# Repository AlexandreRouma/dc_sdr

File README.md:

# DEFCON SDR Badge

The firmware included here is not finished and the hardware isn't fully tested. Use at your own risk.

Make sure to read the license (the file is `/license`). The entire content of this repository is **NOT for commercial purposes**.

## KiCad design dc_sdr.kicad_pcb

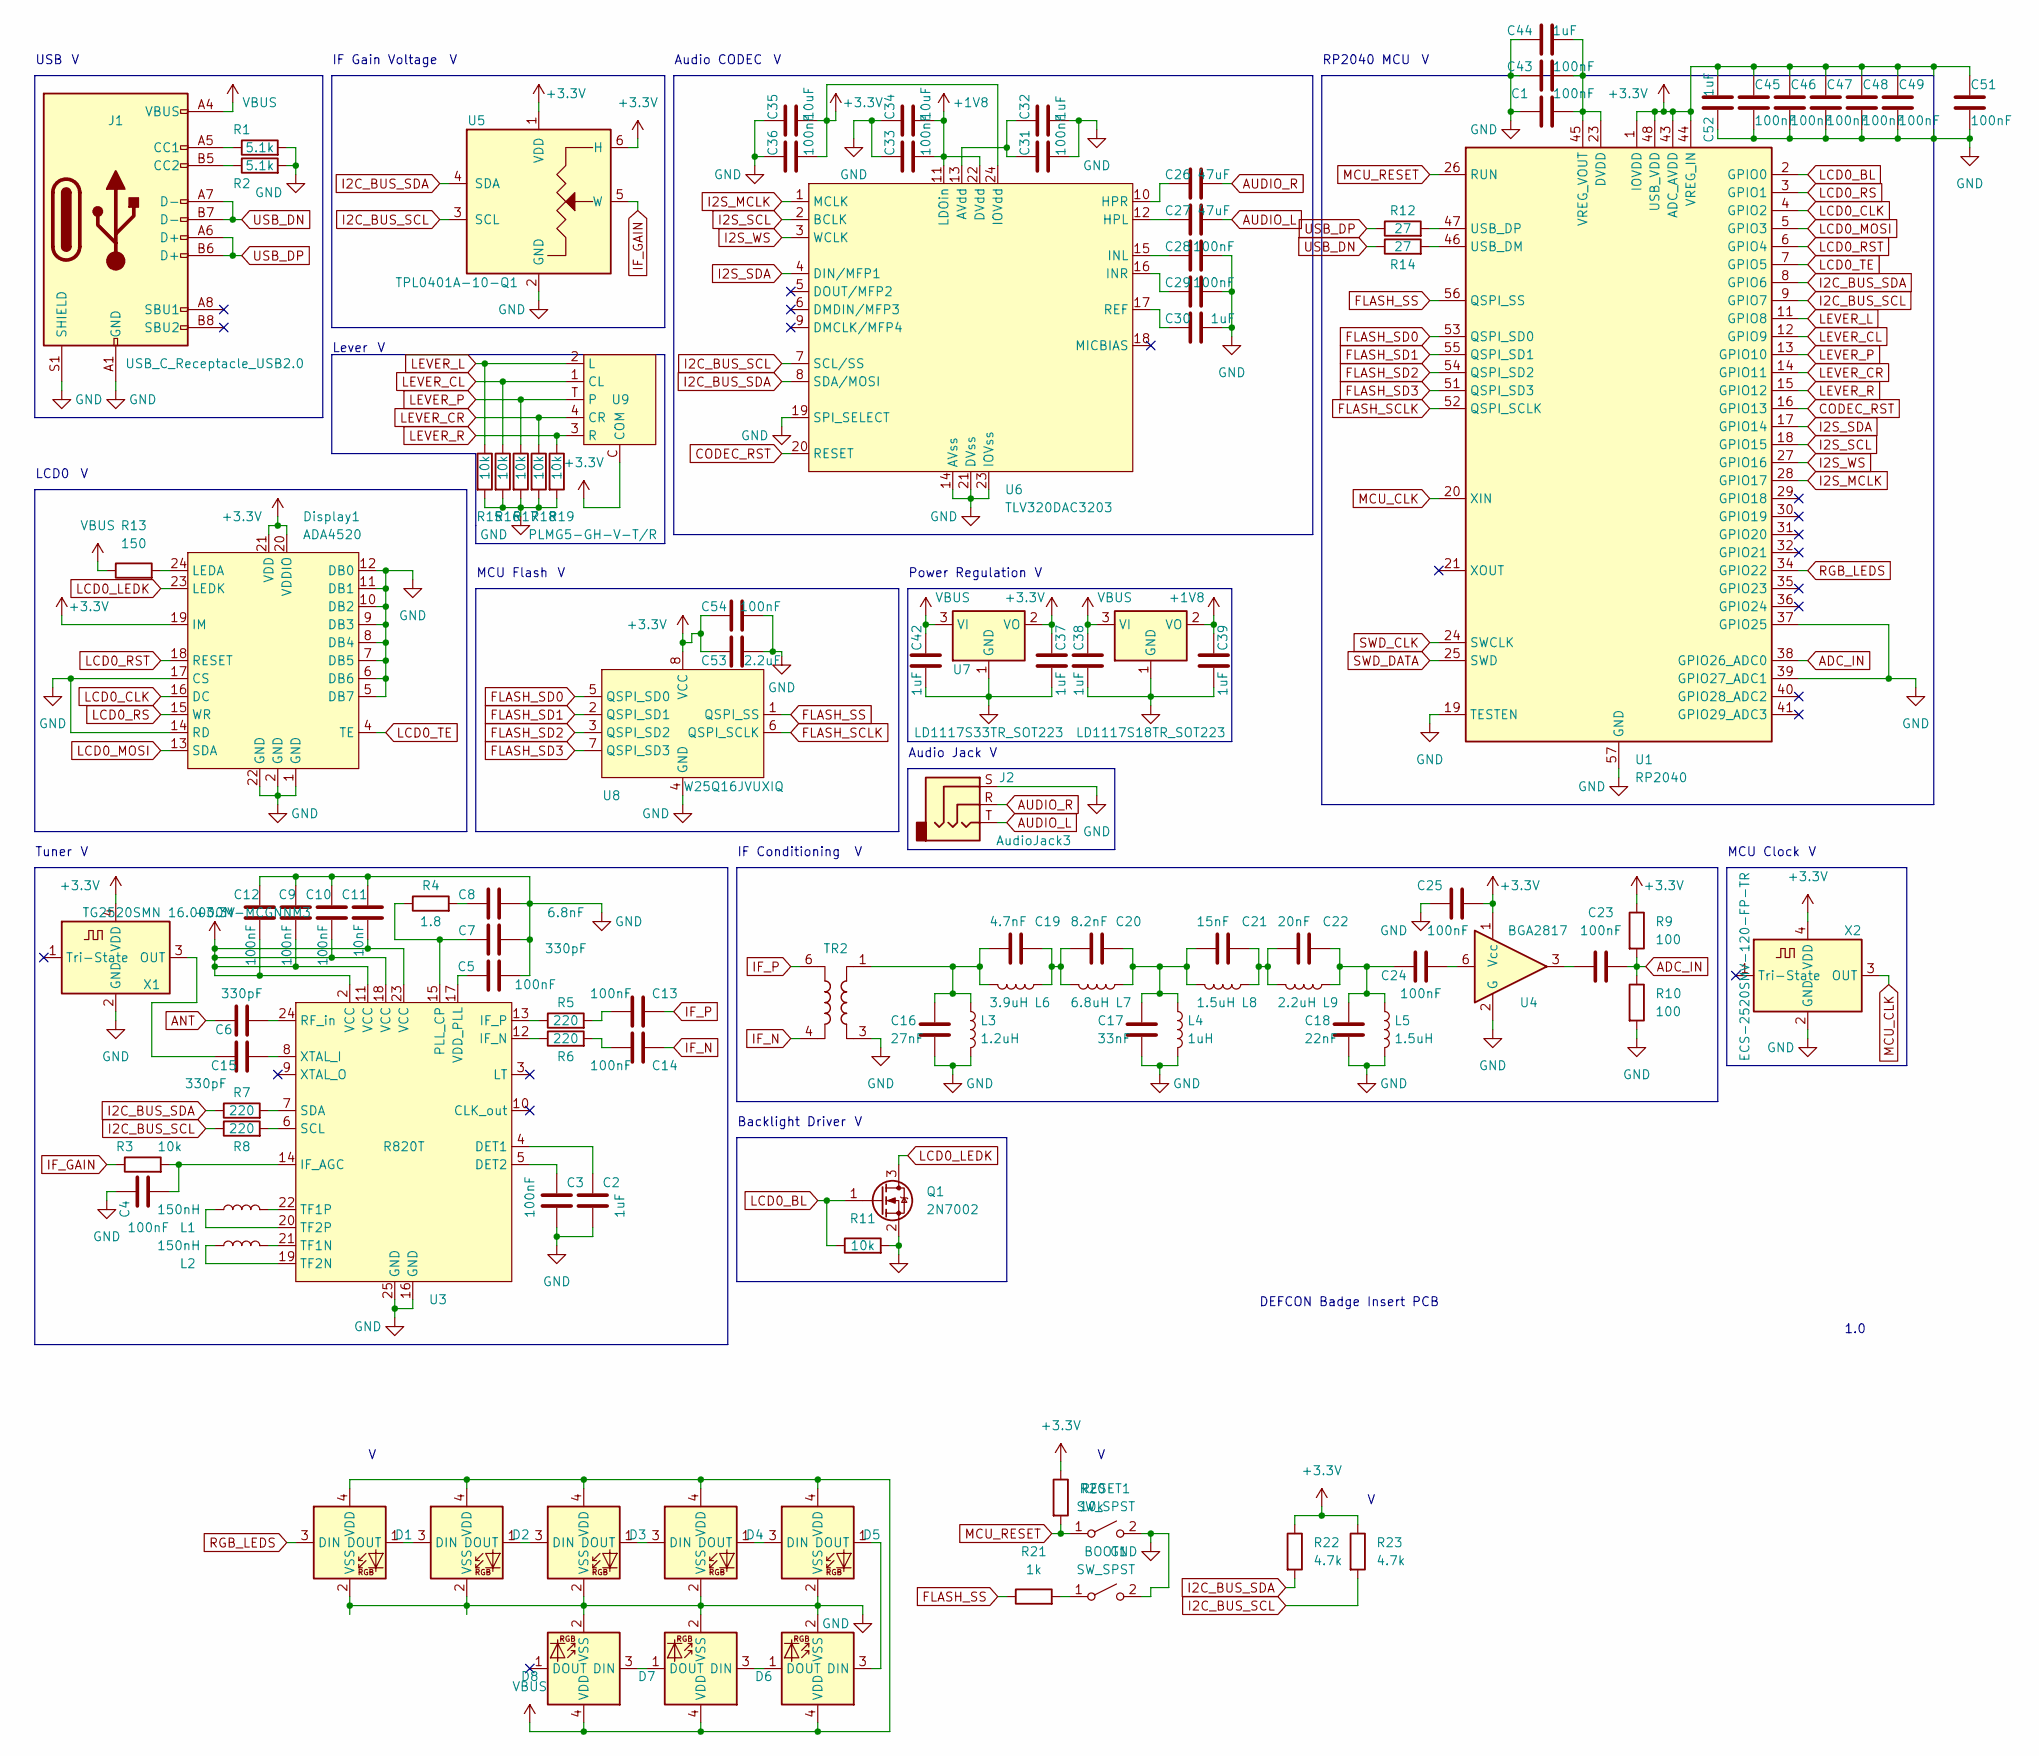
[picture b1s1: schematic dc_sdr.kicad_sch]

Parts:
BOOT1: SW_SPST; SW_SPST_B3U-1000P-B
C1, C3, C4, C5, C9, C10, C12, C13, C14, C23, C24, C25, C28, C29, C31, C33, C36, C43, C45, C46, C47, C48, C49, C51, C54: 100nF; C_0805_2012Metric_Pad1.18x1.45mm_HandSolder
C2, C30, C32, C37, C38, C39, C42, C44, C52: 1uF; C_0805_2012Metric_Pad1.18x1.45mm_HandSolder
C6, C7, C15: 330pF; C_0805_2012Metric_Pad1.18x1.45mm_HandSolder
C8: 6.8nF; C_0805_2012Metric_Pad1.18x1.45mm_HandSolder
C11: 10nF; C_0805_2012Metric_Pad1.18x1.45mm_HandSolder
C16: 27nF; C_0805_2012Metric_Pad1.18x1.45mm_HandSolder
C17: 33nF; C_0805_2012Metric_Pad1.18x1.45mm_HandSolder
C18: 22nF; C_0805_2012Metric_Pad1.18x1.45mm_HandSolder
C19: 4.7nF; C_0805_2012Metric_Pad1.18x1.45mm_HandSolder
C20: 8.2nF; C_0805_2012Metric_Pad1.18x1.45mm_HandSolder
C21: 15nF; C_0805_2012Metric_Pad1.18x1.45mm_HandSolder
C22: 20nF; C_0805_2012Metric_Pad1.18x1.45mm_HandSolder
C26, C27: 47uF; C_0805_2012Metric_Pad1.18x1.45mm_HandSolder
C34, C35: 10uF; C_0805_2012Metric_Pad1.18x1.45mm_HandSolder
C53: 2.2uF; C_0805_2012Metric_Pad1.18x1.45mm_HandSolder
D1, D2, D3, D4, D5, D6, D7, D8: LED_WS2812B-2020_PLCC4_2.0x2.0mm
Display1: ADA4520; AMPHENOL_SFV24R-2STE1HLF
J1: USB_C_Receptacle_USB2.0; USB_C_Receptacle_GCT_USB4105-xx-A_16P_TopMnt_Horizontal
J2: AudioJack3; Jack_3.5mm_CUI_SJ-3523-SMT_Horizontal
L1, L2: 150nH; L_0805_2012Metric_Pad1.15x1.40mm_HandSolder
L3: 1.2uH; L_0805_2012Metric_Pad1.15x1.40mm_HandSolder
L4: 1uH; L_0805_2012Metric_Pad1.15x1.40mm_HandSolder
L5, L8: 1.5uH; L_0805_2012Metric_Pad1.15x1.40mm_HandSolder
L6: 3.9uH; L_0805_2012Metric_Pad1.15x1.40mm_HandSolder
L7: 6.8uH; L_0805_2012Metric_Pad1.15x1.40mm_HandSolder
L9: 2.2uH; L_0805_2012Metric_Pad1.15x1.40mm_HandSolder
Q1: 2N7002; SOT-23
R1, R2: 5.1k; R_0805_2012Metric_Pad1.20x1.40mm_HandSolder
R3, R11, R15, R16, R17, R18, R19, R20: 10k; R_0805_2012Metric_Pad1.20x1.40mm_HandSolder
R4: 1.8; R_0805_2012Metric_Pad1.20x1.40mm_HandSolder
R5, R6, R7, R8: 220; R_0805_2012Metric_Pad1.20x1.40mm_HandSolder
R9, R10: 100; R_0805_2012Metric_Pad1.20x1.40mm_HandSolder
R12, R14: 27; R_0805_2012Metric_Pad1.20x1.40mm_HandSolder
R13: 150; R_0805_2012Metric_Pad1.20x1.40mm_HandSolder
R21: 1k; R_0805_2012Metric_Pad1.20x1.40mm_HandSolder
R22, R23: 4.7k; R_0805_2012Metric_Pad1.20x1.40mm_HandSolder
RESET1: SW_SPST; SW_SPST_B3U-1000P-B
TR2: Transformer_MiniCircuits_AT224-1A
U1: RP2040; QFN-56-1EP_7x7mm_P0.4mm_EP3.2x3.2mm
U3: R820T; QFN-24-1EP_4x4mm_P0.5mm_EP2.8x2.8mm
U4: BGA2817; SOT-363_SC-70-6
U5: TPL0401A-10-Q1; Texas_R-PDSO-G6
U6: TLV320DAC3203; VQFN-24-1EP_4x4mm_P0.5mm_EP2.5x2.5mm
U7: LD1117S33TR_SOT223; SOT-223-3_TabPin2
U8: W25Q16JVUXIQ; SON50P300X200X60-9N
U9: PLMG5-GH-V-T/R; PLMG5-GH-V-T_R
U11: LD1117S18TR_SOT223; SOT-223-3_TabPin2
X1: TG2520SMN 16.0000M-MCGNNM3; Oscillator_SMD_ECS_2520MV-xxx-xx-4Pin_2.5x2.0mm
X2: ECS-2520SMV-120-FP-TR; Oscillator_SMD_ECS_2520MV-xxx-xx-4Pin_2.5x2.0mm

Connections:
+1V8: C33.2, C34.2, C39.1, U6.11 (LDOin), U6.22 (DVdd), U11.2 (VO)
+3.3V: C9.2, C10.2, C11.2, C12.2, C25.2, C35.2, C36.2, C37.1, C45.1, C46.1, C47.1, C48.1, C49.1, C51.1, C52.2, C53.1, C54.1, Display1.19 (IM), Display1.20 (VDDIO), Display1.21 (VDD), R9.1, R20.1, R22.1, R23.1, U1.1 (IOVDD), U1.10 (IOVDD), U1.22 (IOVDD), U1.33 (IOVDD), U1.42 (IOVDD), U1.43 (ADC_AVDD), U1.44 (VREG_IN), U1.48 (USB_VDD), U1.49 (IOVDD), U3.2 (VCC), U3.11 (VCC), U3.18 (VCC), U3.23 (VCC), U4.1 (Vcc), U5.1 (VDD), U5.6 (H), U6.24 (IOVdd), U7.2 (VO), U8.8 (VCC), U9.C (COM), X1.4 (VDD), X2.4 (VDD); also elsewhere on the board
ADC_IN: C23.2, R9.2, R10.1, U1.38 (GPIO26_ADC0)
ANT: C6.1
AUDIO_L: C27.2, J2.T
AUDIO_R: C26.2, J2.R
CODEC_RST: U1.16 (GPIO13), U6.20 (RESET)
FLASH_SCLK: U1.52 (QSPI_SCLK), U8.6 (QSPI_SCLK)
FLASH_SD0: U1.53 (QSPI_SD0), U8.5 (QSPI_SD0)
FLASH_SD1: U1.55 (QSPI_SD1), U8.2 (QSPI_SD1)
FLASH_SD2: U1.54 (QSPI_SD2), U8.3 (QSPI_SD2)
FLASH_SD3: U1.51 (QSPI_SD3), U8.7 (QSPI_SD3)
FLASH_SS: R21.1, U1.56 (QSPI_SS), U8.1 (QSPI_SS)
GND: BOOT1.2 (B), C1.1, C2.2, C3.2, C4.1, C5.2, C7.2, C8.2, C9.1, C10.1, C11.1, C12.1, C16.2, C17.2, C18.2, C25.1, C28.2, C29.2, C30.2, C31.2, C32.2, C33.1, C34.1, C35.1, C36.1, C37.2, C38.2, C39.2, C42.2, C43.1, C44.1, C45.2, C46.2, C47.2, C48.2, C49.2, C51.2, C52.1, C53.2, C54.2, D1.2 (VSS), D2.2 (VSS), D3.2 (VSS), D4.2 (VSS), D5.2 (VSS), D6.2 (VSS), D7.2 (VSS), D8.2 (VSS), Display1.1 (GND), Display1.2 (GND), Display1.5 (DB7), Display1.6 (DB6), Display1.7 (DB5), Display1.8 (DB4), Display1.9 (DB3), Display1.10 (DB2), Display1.11 (DB1), Display1.12 (DB0), Display1.14 (RD), Display1.17 (CS), Display1.22 (GND), J1.A1 (GND), J1.A12 (GND), J1.B1 (GND), J1.B12 (GND), J1.S1 (SHIELD), J2.S, L3.2, L4.2, L5.2, Q1.2 (S), R1.2, R2.2, R10.2, R11.2, R15.2, R16.2, R17.2, R18.2, R19.2, RESET1.2 (B), TR2.3, U1.19 (TESTEN), U1.37 (GPIO25), U1.39 (GPIO27_ADC1), U1.57 (GND), U3.16 (GND), U3.25 (GND), U4.2 (G), U4.4 (G), U4.5 (G), U5.2 (GND), U6.14 (AVss), U6.19 (SPI_SELECT), U6.21 (DVss), U6.23 (IOVss), U7.1 (GND), U8.4 (GND), U11.1 (GND), X1.2 (GND), X2.2 (GND); also elsewhere on the board
I2C_BUS_SCL: R8.1, R23.2, U1.9 (GPIO7), U5.3 (SCL), U6.7 (SCL/SS)
I2C_BUS_SDA: R7.1, R22.2, U1.8 (GPIO6), U5.4 (SDA), U6.8 (SDA/MOSI)
I2S_MCLK: U1.28 (GPIO17), U6.1 (MCLK)
I2S_SCL: U1.18 (GPIO15), U6.2 (BCLK)
I2S_SDA: U1.17 (GPIO14), U6.4 (DIN/MFP1)
I2S_WS: U1.27 (GPIO16), U6.3 (WCLK)
IF_GAIN: R3.1, U5.5 (W)
IF_N: C14.2, TR2.4
IF_P: C13.2, TR2.6
LCD0_BL: Q1.1 (G), R11.1, U1.2 (GPIO0)
LCD0_CLK: Display1.16 (DC), U1.4 (GPIO2)
LCD0_LEDK: Display1.23 (LEDK), Q1.3 (D)
LCD0_MOSI: Display1.13 (SDA), U1.5 (GPIO3)
LCD0_RS: Display1.15 (WR), U1.3 (GPIO1)
LCD0_RST: Display1.18 (RESET), U1.6 (GPIO4)
LCD0_TE: Display1.4 (TE), U1.7 (GPIO5)
LEVER_CL: R16.1, U1.12 (GPIO9), U9.1 (CL)
LEVER_CR: R18.1, U1.14 (GPIO11), U9.4 (CR)
LEVER_L: R15.1, U1.11 (GPIO8), U9.2 (L)
LEVER_P: R17.1, U1.13 (GPIO10), U9.T
LEVER_R: R19.1, U1.15 (GPIO12), U9.3 (R)
MCU_CLK: U1.20 (XIN), X2.3 (OUT)
MCU_RESET: R20.2, RESET1.1 (A), U1.26 (RUN)
unnamed: BOOT1.1 (A), R21.2
unnamed: C8.1, R4.2
unnamed: C13.1, R5.2
unnamed: C14.1, R6.2
unnamed: C16.1, C19.2, L3.1, L6.2, TR2.1
unnamed: C17.1, C20.1, C21.2, L4.1, L7.1, L8.2
unnamed: C18.1, C22.1, C24.1, L5.1, L9.1
unnamed: C19.1, C20.2, L6.1, L7.2
unnamed: C21.1, C22.2, L8.1, L9.2
unnamed: C23.1, U4.3
unnamed: C24.2, U4.6
unnamed: D1.1 (DOUT), D2.3 (DIN)
unnamed: D2.1 (DOUT), D3.3 (DIN)
unnamed: D3.1 (DOUT), D4.3 (DIN)
unnamed: D4.1 (DOUT), D5.3 (DIN)
unnamed: D5.1 (DOUT), D6.3 (DIN)
unnamed: D6.1 (DOUT), D7.3 (DIN)
unnamed: D7.1 (DOUT), D8.3 (DIN)
unnamed: Display1.24 (LEDA), R13.2
unnamed: J1.A5 (CC1), R1.1
unnamed: J1.B5 (CC2), R2.1
unnamed: R14.2, U1.46 (USB_DM)
unnamed: R12.2, U1.47 (USB_DP)
unnamed: C1.2, C43.2, C44.2, U1.23 (DVDD), U1.45 (VREG_VOUT), U1.50 (DVDD)
unnamed: C2.1, U3.4 (DET1)
unnamed: C3.1, U3.5 (DET2)
unnamed: C4.2, R3.2, U3.14 (IF_AGC)
unnamed: R6.1, U3.12 (IF_N)
unnamed: R5.1, U3.13 (IF_P)
unnamed: C7.1, R4.1, U3.15 (PLL_CP)
unnamed: C6.2, U3.24 (RF_in)
unnamed: R8.2, U3.6 (SCL)
unnamed: R7.2, U3.7 (SDA)
unnamed: L2.2, U3.21 (TF1N)
unnamed: L1.2, U3.22 (TF1P)
unnamed: L2.1, U3.19 (TF2N)
unnamed: L1.1, U3.20 (TF2P)
unnamed: C5.1, U3.17 (VDD_PLL)
unnamed: C15.2, U3.8 (XTAL_I)
unnamed: C31.1, C32.1, U6.13 (AVdd)
unnamed: C27.1, U6.12 (HPL)
unnamed: C26.1, U6.10 (HPR)
unnamed: C28.1, U6.15 (INL)
unnamed: C29.1, U6.16 (INR)
unnamed: C30.1, U6.17 (REF)
unnamed: C15.1, X1.3 (OUT)
RGB_LEDS: D1.3 (DIN), U1.34 (GPIO22)
SWD_CLK: U1.24 (SWCLK)
SWD_DATA: U1.25 (SWD)
USB_DN: J1.A7 (D-), J1.B7 (D-), R14.1
USB_DP: J1.A6 (D+), J1.B6 (D+), R12.1
VBUS: C38.1, C42.1, D1.4 (VDD), D2.4 (VDD), D3.4 (VDD), D4.4 (VDD), D5.4 (VDD), D6.4 (VDD), D7.4 (VDD), D8.4 (VDD), J1.A4 (VBUS), J1.A9 (VBUS), J1.B4 (VBUS), J1.B9 (VBUS), R13.1, U7.3 (VI), U11.3 (VI)

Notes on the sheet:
DEFCON Badge Insert PCB
1.0
IF Conditioning
IF Gain Voltage
LCD0
Lever
Power Regulation
Tuner
USB
Backlight Driver
RP2040 MCU
MCU Clock
MCU Flash
Audio CODEC
Audio Jack

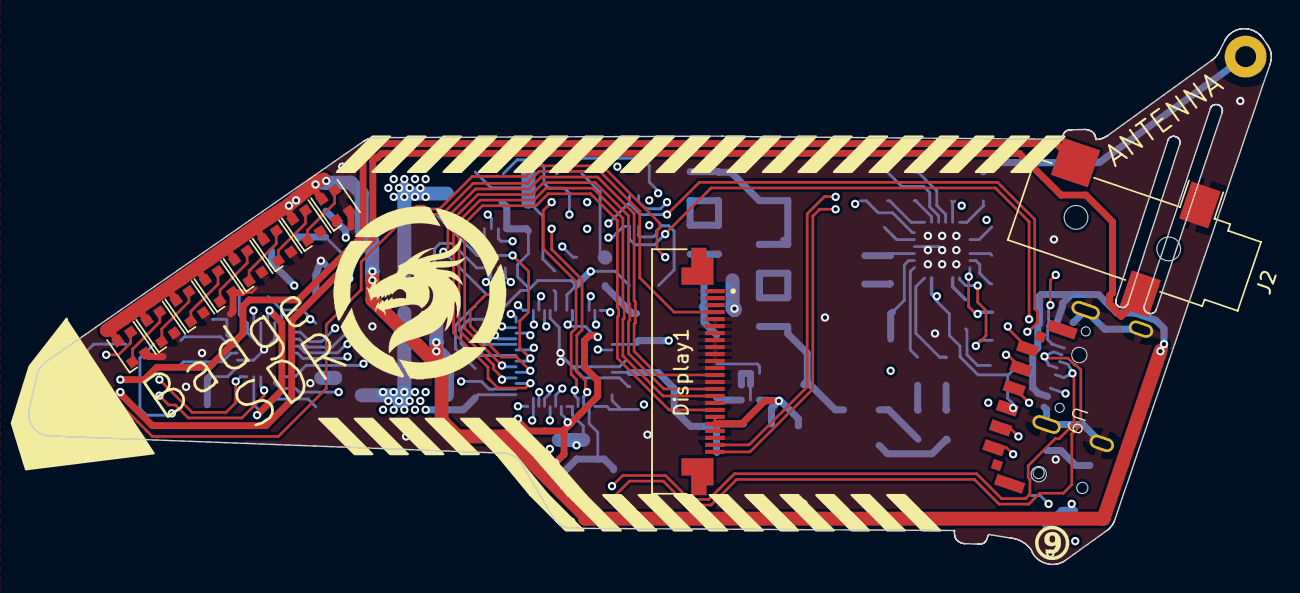
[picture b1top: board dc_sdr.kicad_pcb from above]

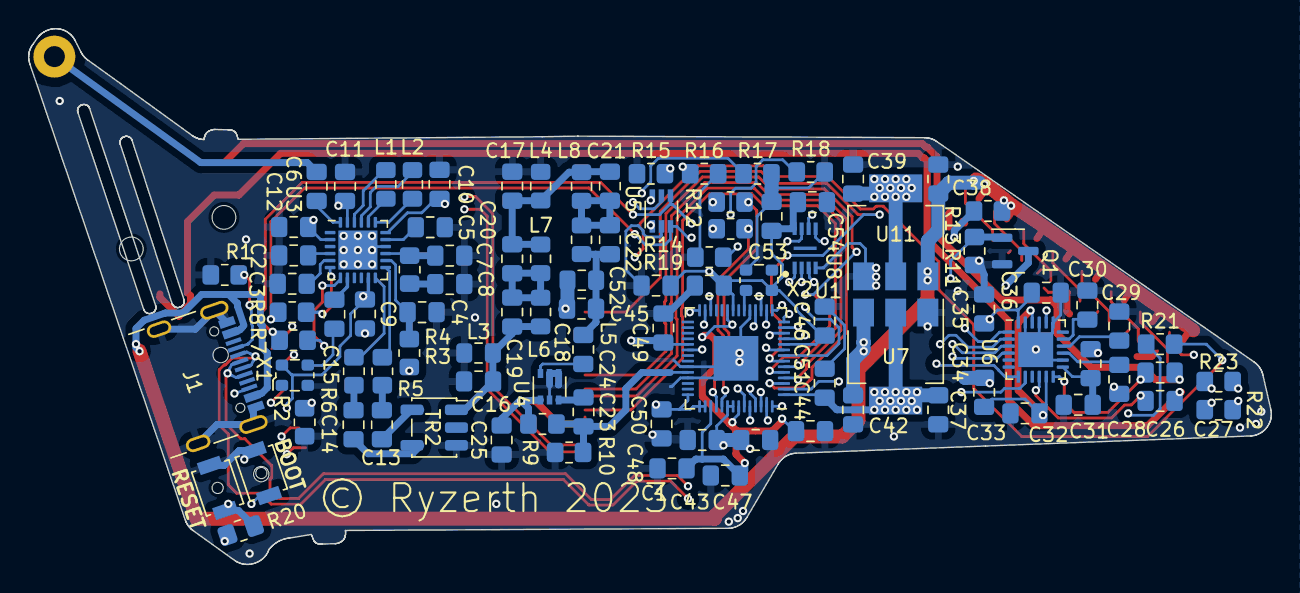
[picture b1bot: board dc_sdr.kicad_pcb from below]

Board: 4 copper layers, 88.9 x 38.3 mm, 110 parts (99 on the bottom side), 86 nets.

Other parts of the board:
C50: 100nF; C_0805_2012Metric_Pad1.18x1.45mm_HandSolder

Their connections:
+3.3V: C50.1; also elsewhere on the board
GND: C50.2; also elsewhere on the board

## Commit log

2023-08-01 work
2023-08-17 more work done

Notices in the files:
dc_sdr.kicad_pcb:
© Ryzerth 2023
